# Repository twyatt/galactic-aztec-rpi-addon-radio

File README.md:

# About

Custom Raspberry Pi Add-on board used during the launch of the [Galactic Aztec] rocket to transmit telemetry data. The board was designed to be stackable with other add-on boards via the designated [pin configuration].

Custom EagleCAD parts on this board can be found in the [SDSU Rocket Eagle Libraries].

# Bill of Materials
| Qty | Description                                     | Part Number         | Vendor        |
|:---:|-------------------------------------------------|--------------------:|---------------|
| 1   | LED Green Vf=1.7V If=2mA 0603                   | [475-1193-1-ND]     | DigiKey       |
| 1   | LED Red Vf=1.8V If=2mA 0603                     | [475-1195-2-ND]     | DigiKey       |
| 1   | LED Yellow Vf=1.8V If=2mA 0603                  | [475-1196-1-ND]     | DigiKey       |
| 3   | MOSFET N-Channel 50V 220mA SOT-23               | [BSS138CT-ND]       | DigiKey       |
| 2   | Resistor 1.8kΩ 1/4W 1% 0603                     | [P1.8KBYCT-ND]      | DigiKey       |
| 7   | Resistor 10kΩ 1/4W 1% 0603                      | [P10KBYCT-ND]       | DigiKey       |
| 1   | Resistor 820Ω 1/4W 1% 0603                      | [P820BYCT-ND]       | DigiKey       |
| 1   | Header 2x10 2mm Pitch                           | [S5750-10-ND]       | DigiKey       |
| 1   | Header Female 1x4 0.1" Pitch                    | [S7037-ND]          | DigiKey       |
| 1   | Header Stacking 2x20 Tall 23mm                  | [1979]              | Adafruit      |
| 1   | 100 ct. No. 4 Nylon Spacer 3/16" OD 1/4" Length | [94639A706]         | McMaster-Carr |
| 1   | 100 ct. 18-8 Stainless Steel Screw 4-40 7/16"   | [91772A109]         | McMaster-Carr |
| 1   | XTend 900 900Mhz 1W                             | [XT09-SI-ND]        | DigiKey       |

[Galactic Aztec]: http://rocket.sdsu.edu/rockets
[pin configuration]: https://docs.google.com/spreadsheets/d/1zGslKhH-ZteeA8sbbTjQlF-Neb-wJ3quIlFH6I8Cvgs/edit?usp=sharing
[SDSU Rocket Eagle Libraries]: https://github.com/twyatt/SDSURocket-Eagle-Libraries
[475-1193-1-ND]: http://www.digikey.com/product-detail/en/LG%20L29K-F2J1-24/475-1193-1-ND/810354
[475-1195-2-ND]: http://www.digikey.com/product-detail/en/LS%20L29K-H1J2-1-Z/475-1195-1-ND/810356
[475-1196-1-ND]: http://www.digikey.com/product-detail/en/LY%20L29K-H1K2-26-Z/475-1196-1-ND/810357
[BSS138CT-ND]: http://www.digikey.com/product-detail/en/BSS138/BSS138CT-ND/244294
[P1.8KBYCT-ND]: http://www.digikey.com/product-detail/en/ERJ-PA3F1801V/P1.8KBYCT-ND/5036145
[P10KBYCT-ND]: http://www.digikey.com/product-detail/en/ERJ-PA3F1002V/P10KBYCT-ND/5036115
[P820BYCT-ND]: http://www.digikey.com/product-detail/en/ERJ-PA3F8200V/P820BYCT-ND/5036224
[S5750-10-ND]: http://www.digikey.com/product-detail/en/NPPN102AFCN-RC/S5750-10-ND/804795
[S7037-ND]: http://www.digikey.com/product-detail/en/PPPC041LFBN-RC/S7037-ND/810176
[1979]: http://www.adafruit.com/products/1979
[94639A706]: http://www.mcmaster.com/#94639a620/=weyw3h
[91772A109]: http://www.mcmaster.com/#91772a109/=wau506
[XT09-SI-ND]: http://www.digikey.com/product-detail/en/XT09-SI/XT09-SI-ND/688312

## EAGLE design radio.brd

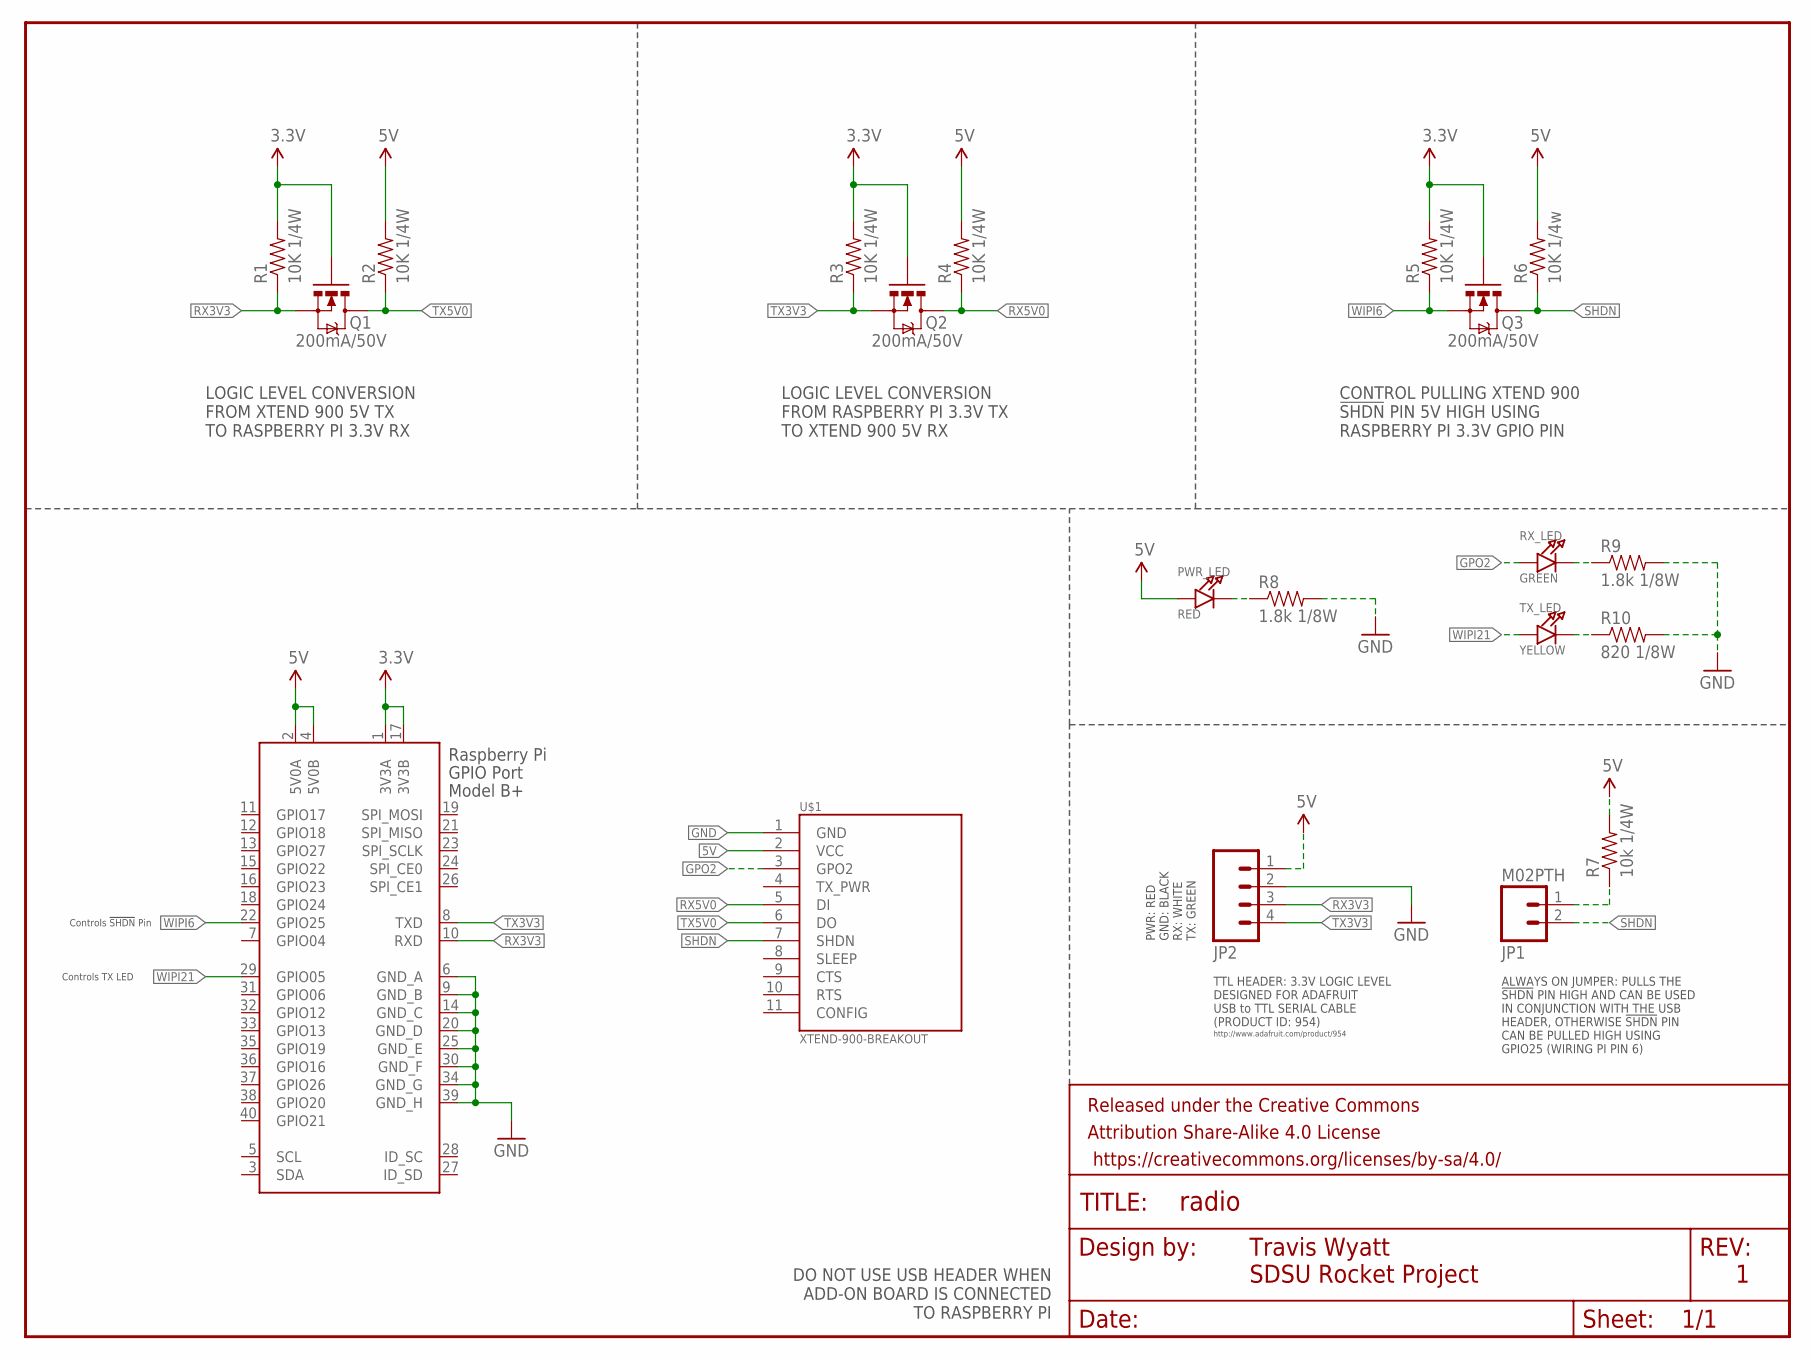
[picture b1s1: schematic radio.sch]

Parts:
FRAME1: FRAME-LETTER; CREATIVE_COMMONS
JP1: M02PTH; 1X02
JP2: M04PTH; 1X04
PWR_LED: RED; CHIPLED_0603
Q1, Q2, Q3: 200mA/50V; SOT23-3
R1, R2, R3, R4, R5: 10K 1/4W; 0603-RES
R6: 10K 1/4w; 0603-RES
R7: 10k 1/4W; 0603-RES
R8, R9: 1.8k 1/8W; 0603-RES
R10: 820 1/8W; 0603-RES
RX_LED: GREEN; CHIPLED_0603
TX_LED: YELLOW; CHIPLED_0603
U$1: XTEND-900-BREAKOUT; XTEND-900
X1: RASPI_BOARD_B+#_H; RASPI_BOARD_B+HAT

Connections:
3.3V: Q1.1 (G), Q2.1 (G), Q3.1 (G), R1.2, R3.2, R5.2, X1.1 (3V3A), X1.17 (3V3B)
5V: JP2.1, PWR_LED.A, R2.2, R4.2, R6.2, R7.2, U$1.2 (VCC), X1.2 (5V0A), X1.4 (5V0B)
GND: JP2.2, R8.2, R9.2, R10.2, U$1.1 (GND), X1.6 (GND_A), X1.9 (GND_B), X1.14 (GND_C), X1.20 (GND_D), X1.25 (GND_E), X1.30 (GND_F), X1.34 (GND_G), X1.39 (GND_H)
GPO2: RX_LED.A, U$1.3 (GPO2)
unnamed: JP1.1, R7.1
unnamed: PWR_LED.C, R8.1
unnamed: R9.1, RX_LED.C
unnamed: R10.1, TX_LED.C
RX3V3: JP2.3, Q1.2 (S), R1.1, X1.10 (RXD)
RX5V0: Q2.3 (D), R4.1, U$1.5 (DI)
SHDN: JP1.2, Q3.3 (D), R6.1, U$1.7 (SHDN)
TX3V3: JP2.4, Q2.2 (S), R3.1, X1.8 (TXD)
TX5V0: Q1.3 (D), R2.1, U$1.6 (DO)
WIPI6: Q3.2 (S), R5.1, X1.22 (GPIO25)
WIPI21: TX_LED.A, X1.29 (GPIO05)

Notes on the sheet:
Travis Wyatt
SDSU Rocket Project
Controls !SHDN! Pin
LOGIC LEVEL CONVERSION FROM RASPBERRY PI 3.3V TX TO XTEND 900 5V RX
LOGIC LEVEL CONVERSION FROM XTEND 900 5V TX TO RASPBERRY PI 3.3V RX
CONTROL PULLING XTEND 900 !SHDN! PIN 5V HIGH USING RASPBERRY PI 3.3V GPIO PIN
PWR: RED GND: BLACK RX: WHITE TX: GREEN
ALWAYS ON JUMPER: PULLS THE !SHDN! PIN HIGH AND CAN BE USED IN CONJUNCTION WITH THE USB HEADER, OTHERWISE !SHDN! PIN CAN BE PULLED HIGH USING GPIO25 (WIRING PI PIN 6)
TTL HEADER: 3.3V LOGIC LEVEL DESIGNED FOR ADAFRUIT USB to TTL SERIAL CABLE (PRODUCT ID: 954)
DO NOT USE USB HEADER WHEN ADD-ON BOARD IS CONNECTED TO RASPBERRY PI
http://www.adafruit.com/product/954
Controls TX LED

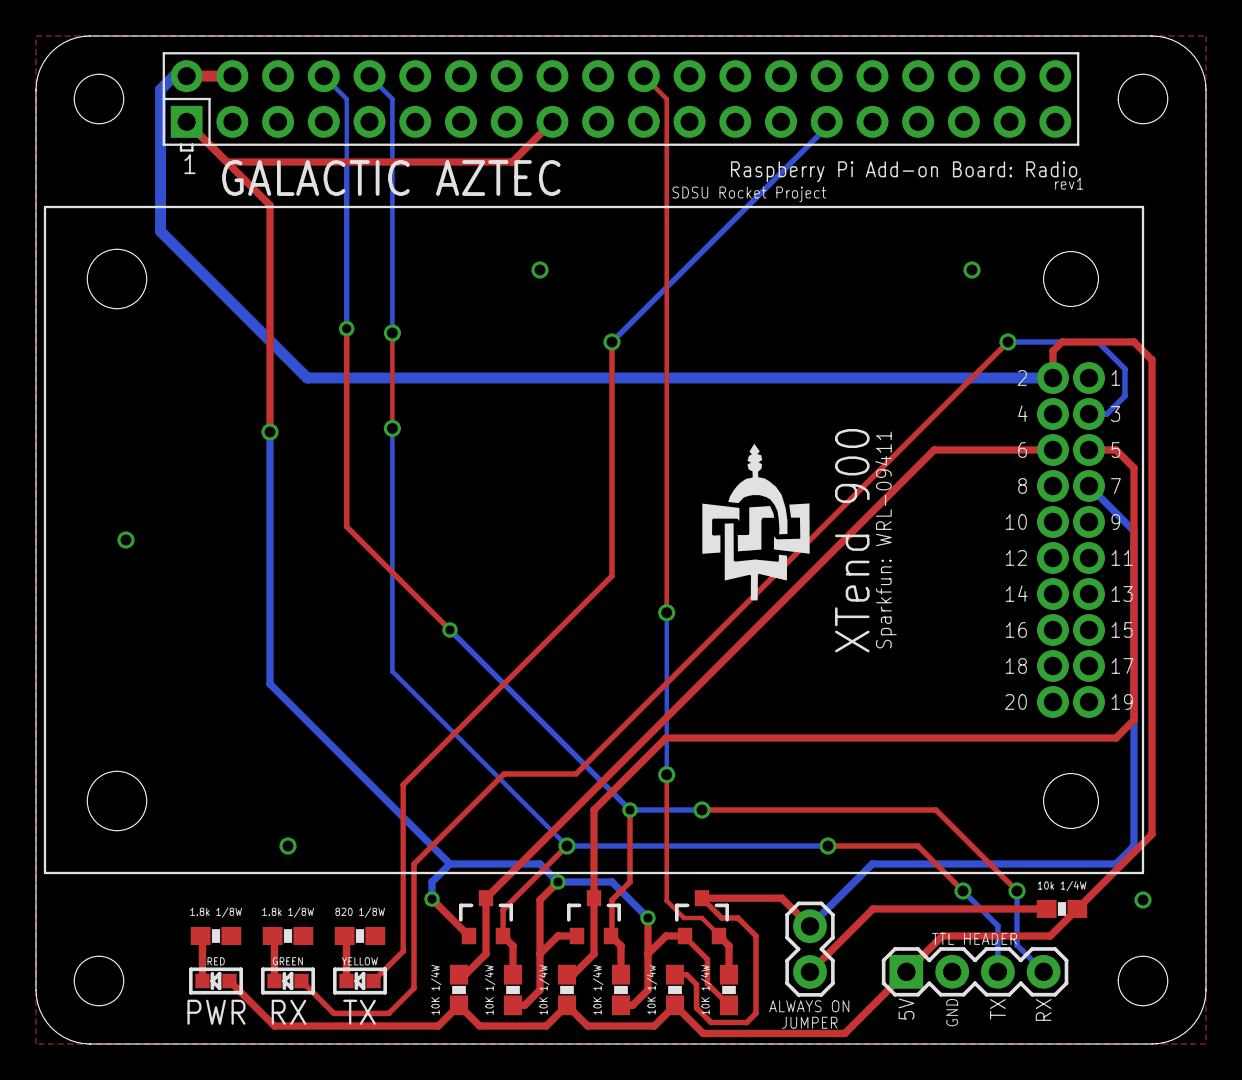
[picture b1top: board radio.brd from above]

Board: 2 copper layers, 65.0 x 56.0 mm, 21 parts (0 on the bottom side), 15 nets.

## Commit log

2017-04-11 Add schematic/board design and artwork
2017-04-12 Add README with brief description and BOM

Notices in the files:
parts and their libraries:
SparkFun-Resistors: Licensing: Creative Commons ShareAlike 4.0 International - https://creativecommons.org/licenses/by-sa/4.0
SparkFun-Aesthetics: Released under the Creative Commons Attribution Share-Alike 4.0 License
SparkFun-Aesthetics: https://creativecommons.org/licenses/by-sa/4.0
